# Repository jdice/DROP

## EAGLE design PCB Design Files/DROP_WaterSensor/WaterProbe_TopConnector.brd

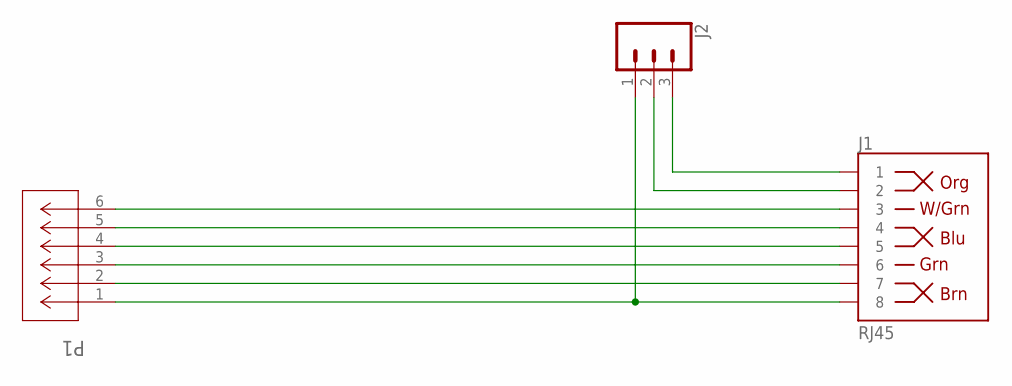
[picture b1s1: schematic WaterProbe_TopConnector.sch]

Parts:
J1: RJ45; RJ45-8
J2: CONN_03; 1X03
P1: 6PINJSTS6B-ZR(LF)(SN); S6B-ZR

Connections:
unnamed: J1.8, J2.1, P1.1
unnamed: J1.7, P1.2
unnamed: J1.6, P1.3
unnamed: J1.5, P1.4
unnamed: J1.4, P1.5
unnamed: J1.3, P1.6
unnamed: J1.1, J2.3
unnamed: J1.2, J2.2

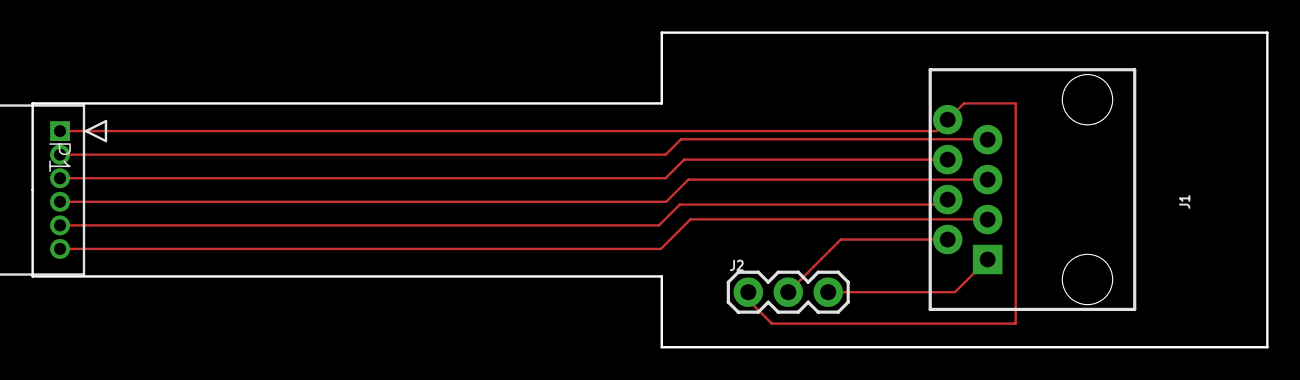
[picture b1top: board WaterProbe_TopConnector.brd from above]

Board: 2 copper layers, 78.5 x 20.0 mm, 3 parts (0 on the bottom side), 8 nets.

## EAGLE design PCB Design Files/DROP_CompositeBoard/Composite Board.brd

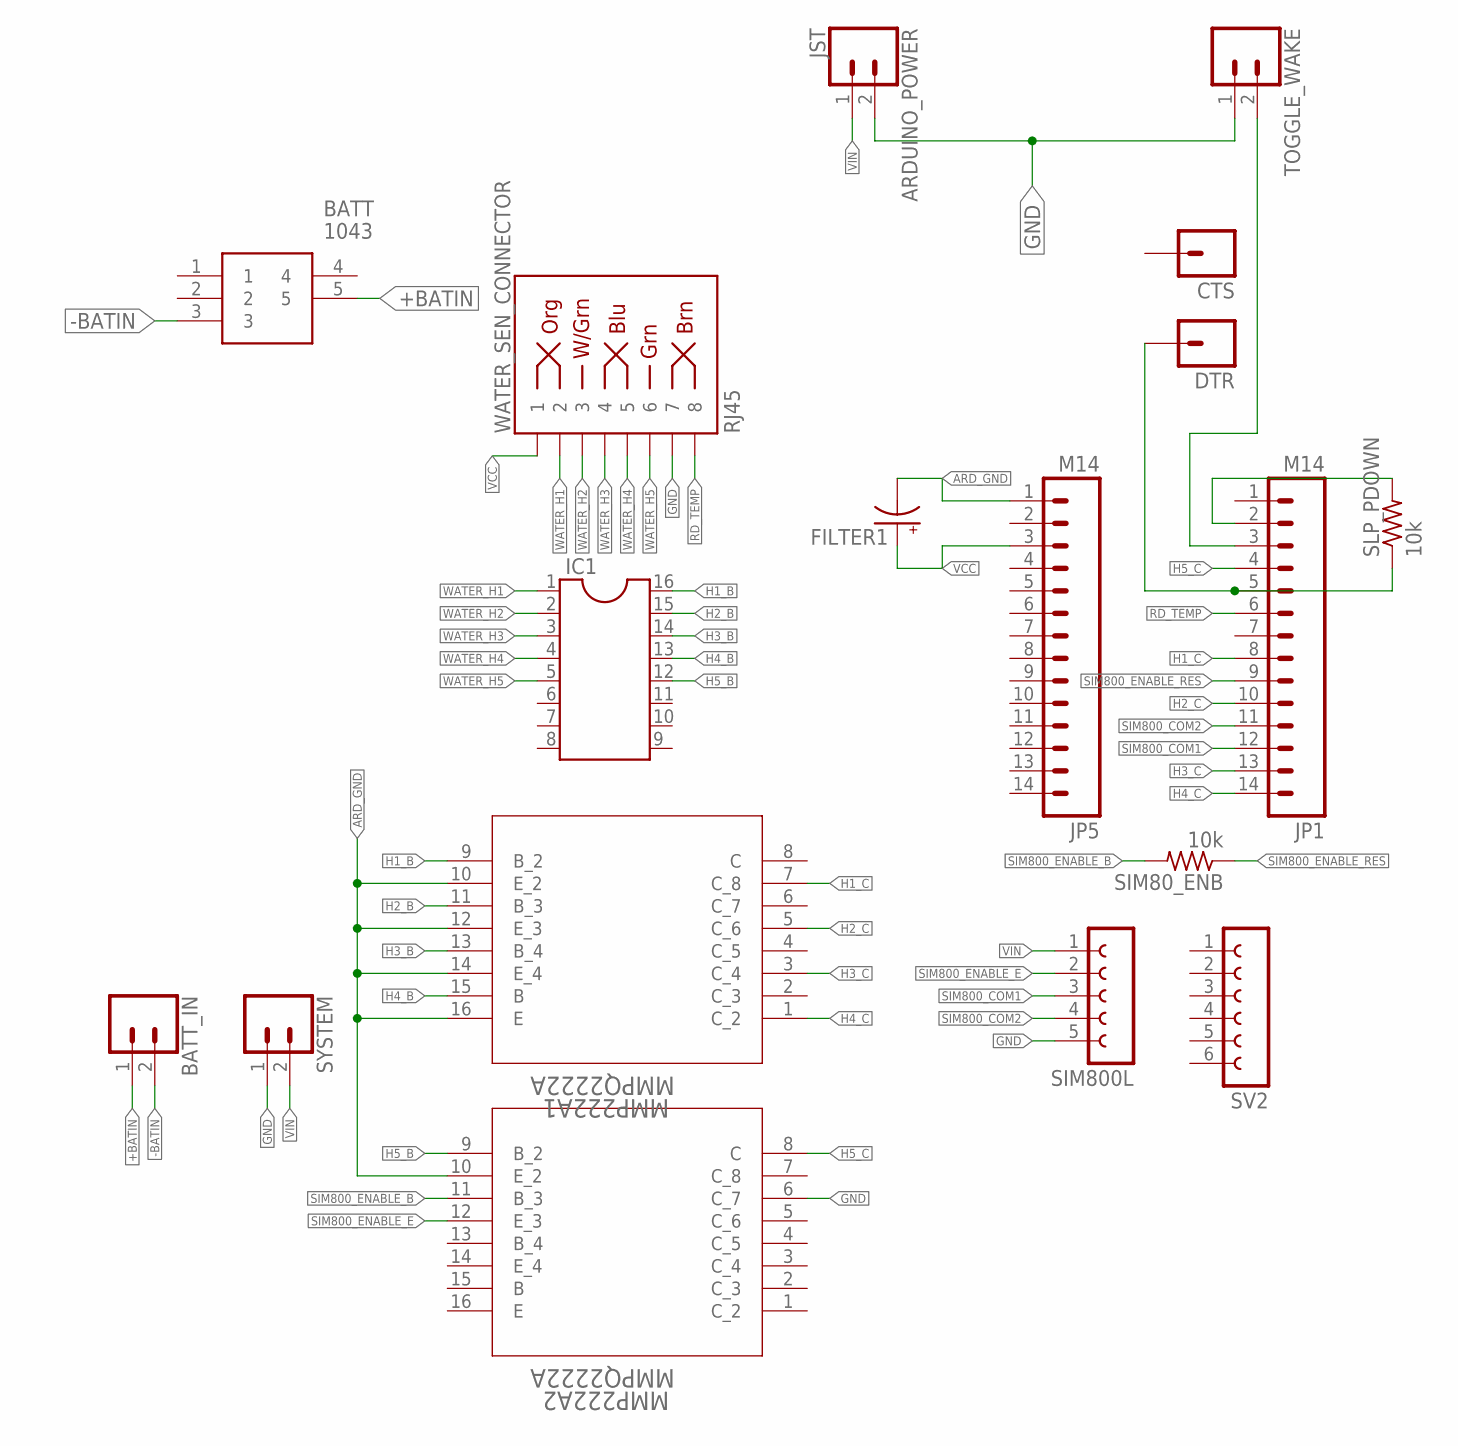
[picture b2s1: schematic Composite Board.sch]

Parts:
ARDUINO_POWER: JST; 1X02
BATT: 1043
BATT_IN: CONN_02; 1X02
CTS: M01PTH; 1X01
DTR: M01PTH; 1X01
FILTER1: CPOL-USE2.5-5; E2,5-5
IC1: DIL16S; SOCKET-16
JP1, JP5: M14; 1X14
MMP222A1, MMP222A2: MMPQ2222A; SO-G16
SIM80_ENB: 10k; 0204/5
SIM800L: FE05-1
SLP_PDOWN: 10k; 0204/5
SV2: FE06-1; FE06
SYSTEM: CONN_02; 1X02
TOGGLE_WAKE: CONN_02; 1X02
WATER_SEN_CONNECTOR: RJ45; RJ45-8

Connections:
+BATIN: BATT.5, BATT_IN.1
-BATIN: BATT.3, BATT_IN.2
ARD_GND: FILTER1.-, JP5.1, MMP222A1.10 (E_2), MMP222A1.12 (E_3), MMP222A1.14 (E_4), MMP222A1.16 (E), MMP222A2.10 (E_2)
GND: ARDUINO_POWER.2, MMP222A2.6 (C_7), SIM800L.5, SYSTEM.1, TOGGLE_WAKE.1, WATER_SEN_CONNECTOR.7
H1_B: IC1.16, MMP222A1.9 (B_2)
H1_C: JP1.8, MMP222A1.7 (C_8)
H2_B: IC1.15, MMP222A1.11 (B_3)
H2_C: JP1.10, MMP222A1.5 (C_6)
H3_B: IC1.14, MMP222A1.13 (B_4)
H3_C: JP1.13, MMP222A1.3 (C_4)
H4_B: IC1.13, MMP222A1.15 (B)
H4_C: JP1.14, MMP222A1.1 (C_2)
H5_B: IC1.12, MMP222A2.9 (B_2)
H5_C: JP1.4, MMP222A2.8 (C)
unnamed: DTR.1, JP1.5, SLP_PDOWN.1
unnamed: JP1.2, SLP_PDOWN.2
unnamed: JP1.3, TOGGLE_WAKE.2
RD_TEMP: JP1.6, WATER_SEN_CONNECTOR.8
SIM800_COM1: JP1.12, SIM800L.3
SIM800_COM2: JP1.11, SIM800L.4
SIM800_ENABLE_B: MMP222A2.11 (B_3), SIM80_ENB.2
SIM800_ENABLE_E: MMP222A2.12 (E_3), SIM800L.2
SIM800_ENABLE_RES: JP1.9, SIM80_ENB.1
VCC: FILTER1.+, JP5.3, WATER_SEN_CONNECTOR.1
VIN: ARDUINO_POWER.1, SIM800L.1, SYSTEM.2
WATER_H1: IC1.1, WATER_SEN_CONNECTOR.2
WATER_H2: IC1.2, WATER_SEN_CONNECTOR.3
WATER_H3: IC1.3, WATER_SEN_CONNECTOR.4
WATER_H4: IC1.4, WATER_SEN_CONNECTOR.5
WATER_H5: IC1.5, WATER_SEN_CONNECTOR.6

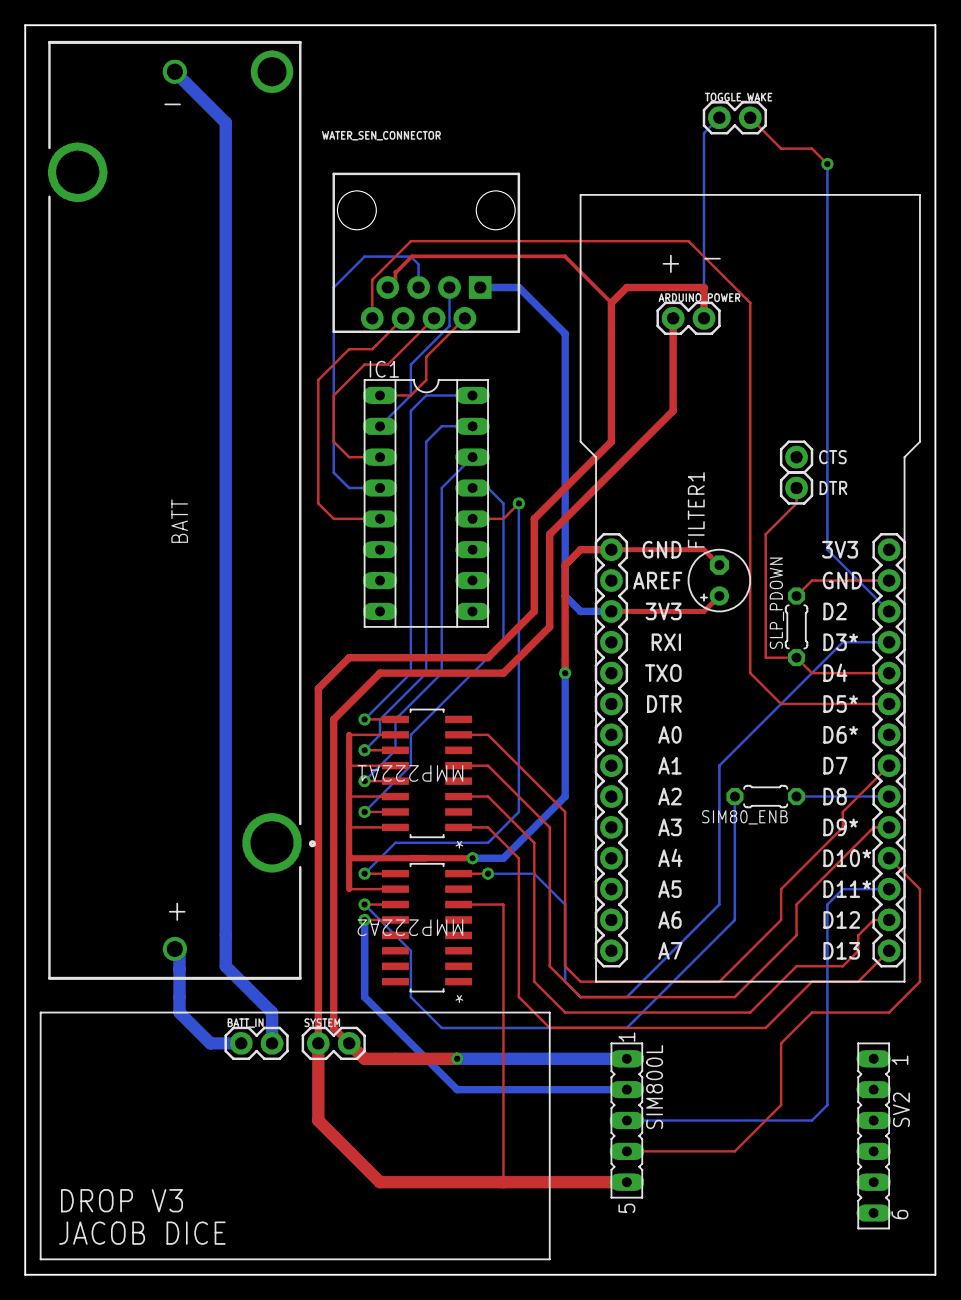
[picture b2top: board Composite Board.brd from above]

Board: 2 copper layers, 74.9 x 102.9 mm, 18 parts (0 on the bottom side), 30 nets.

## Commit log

2019-02-03 Initializing repository. No changes since submission of main board for manufacturing.
2019-03-24 Submitted to defense committee for revision and review

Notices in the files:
parts and their libraries:
SparkFun-Connectors: Licensing: Creative Commons ShareAlike 4.0 International - https://creativecommons.org/licenses/by-sa/4.0
